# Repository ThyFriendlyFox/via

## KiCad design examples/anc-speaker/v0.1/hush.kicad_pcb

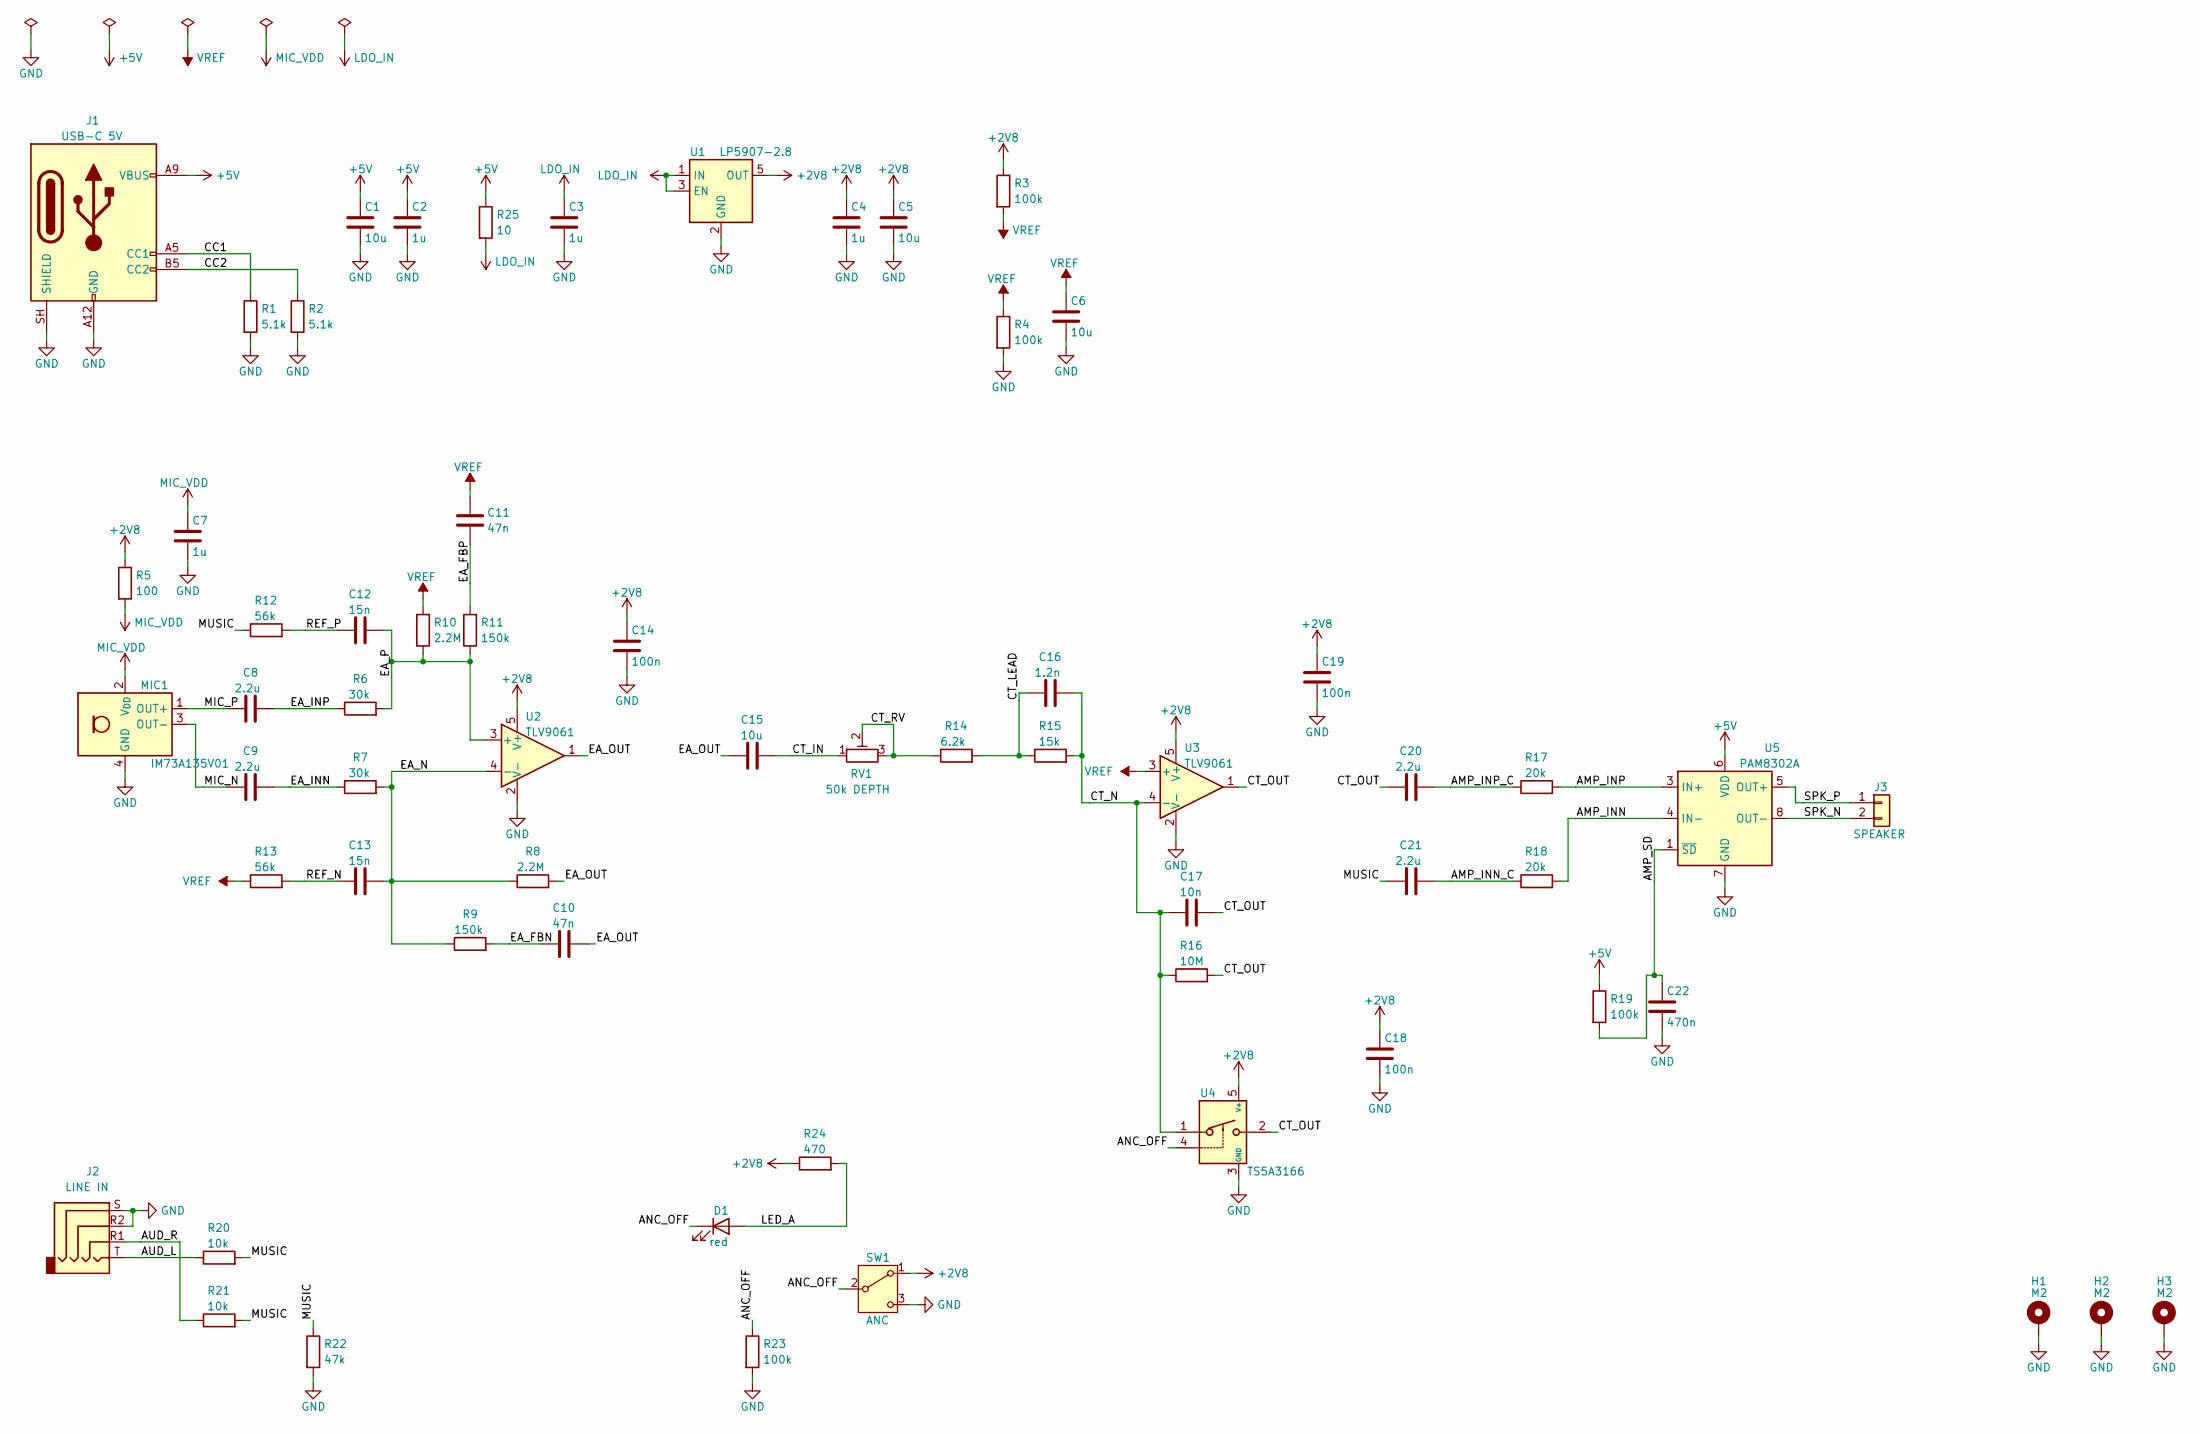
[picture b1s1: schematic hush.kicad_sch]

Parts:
C1: 10u; C_0805_2012Metric
C2, C3, C4, C7: 1u; C_0402_1005Metric
C5, C6, C15: 10u; C_0603_1608Metric
C8, C9, C20, C21: 2.2u; C_0402_1005Metric
C10, C11: 47n; C_0603_1608Metric
C12, C13: 15n; C_0402_1005Metric
C14, C18, C19: 100n; C_0402_1005Metric
C16: 1.2n; C_0402_1005Metric
C17: 10n; C_0402_1005Metric
C22: 470n; C_0402_1005Metric
D1: red; LED_0603_1608Metric
H1, H2, H3: M2; MountingHole_2.2mm_M2_ISO7380_Pad
J1: USB-C 5V; USB_C_Receptacle_GCT_USB4125-xx-x_6P_TopMnt_Horizontal
J2: LINE IN; Jack_3.5mm_PJ320D_Horizontal
J3: SPEAKER; SolderWire-0.25sqmm_1x02_P4.2mm_D0.65mm_OD1.7mm
MIC1: IM73A135V01; Infineon_PG-LLGA-5-2
R1, R2: 5.1k; R_0402_1005Metric
R3, R4, R19, R23: 100k; R_0402_1005Metric
R5: 100; R_0402_1005Metric
R6, R7: 30k; R_0402_1005Metric
R8, R10: 2.2M; R_0402_1005Metric
R9, R11: 150k; R_0402_1005Metric
R12, R13: 56k; R_0402_1005Metric
R14: 6.2k; R_0402_1005Metric
R15: 15k; R_0402_1005Metric
R16: 10M; R_0402_1005Metric
R17, R18: 20k; R_0402_1005Metric
R20, R21: 10k; R_0402_1005Metric
R22: 47k; R_0402_1005Metric
R24: 470; R_0402_1005Metric
R25: 10; R_0402_1005Metric
RV1: 50k DEPTH; Potentiometer_Bourns_TC33X_Vertical
SW1: ANC; SW_SPDT_PCM12
U1: LP5907-2.8; SOT-23-5
U2, U3: TLV9061; SOT-23-5
U4: TS5A3166; SOT-353_SC-70-5
U5: PAM8302A; MSOP-8_3x3mm_P0.65mm

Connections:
+2V8: C4.1, C5.1, C14.1, C18.1, C19.1, R3.1, R5.1, R24.1, SW1.1 (A), U1.5 (OUT), U2.5 (V+), U3.5 (V+), U4.5 (V+)
+5V: C1.1, C2.1, J1.A9 (VBUS), J1.B9 (VBUS), R19.1, R25.1, U5.6 (VDD)
/AMP_INN: R18.2, U5.4 (IN-)
/AMP_INN_C: C21.2, R18.1
/AMP_INP: R17.2, U5.3 (IN+)
/AMP_INP_C: C20.2, R17.1
/AMP_SD: C22.1, R19.2, U5.1 (~SD)
/ANC_OFF: D1.1 (K), R23.1, SW1.2 (B), U4.4
/AUD_L: J2.T, R20.1
/AUD_R: J2.R1, R21.1
/CC1: J1.A5 (CC1), R1.1
/CC2: J1.B5 (CC2), R2.1
/CT_IN: C15.2, RV1.1
/CT_LEAD: C16.1, R14.2, R15.1
/CT_N: C16.2, C17.1, R15.2, R16.1, U3.4 (-), U4.1
/CT_OUT: C17.2, C20.1, R16.2, U3.1, U4.2
/CT_RV: R14.1, RV1.2, RV1.3
/EA_FBN: C10.1, R9.2
/EA_FBP: C11.1, R11.2
/EA_INN: C9.2, R7.1
/EA_INP: C8.2, R6.1
/EA_N: C13.2, R7.2, R8.1, R9.1, U2.4 (-)
/EA_OUT: C10.2, C15.1, R8.2, U2.1
/EA_P: C12.2, R6.2, R10.1, R11.1, U2.3 (+)
/LED_A: D1.2 (A), R24.2
/MIC_N: C9.1, MIC1.3 (OUT-)
/MIC_P: C8.1, MIC1.1 (OUT+)
/MUSIC: C21.1, R12.1, R20.2, R21.2, R22.1
/REF_N: C13.1, R13.2
/REF_P: C12.1, R12.2
/SPK_N: J3.2, U5.8 (OUT-)
/SPK_P: J3.1, U5.5 (OUT+)
GND: C1.2, C2.2, C3.2, C4.2, C5.2, C6.2, C7.2, C14.2, C18.2, C19.2, C22.2, H1.1, H2.1, H3.1, J1.A12 (GND), J1.B12 (GND), J1.SH (SHIELD), J2.R2, J2.S, MIC1.4 (GND), MIC1.5 (GND), R1.2, R2.2, R4.2, R22.2, R23.2, SW1.3 (C), U1.2 (GND), U2.2 (V-), U3.2 (V-), U4.3 (GND), U5.7 (GND)
LDO_IN: C3.1, R25.2, U1.1 (IN), U1.3 (EN)
MIC_VDD: C7.1, MIC1.2 (V_{DD}), R5.2
VREF: C6.1, C11.2, R3.2, R4.1, R10.2, R13.1, U3.3 (+)

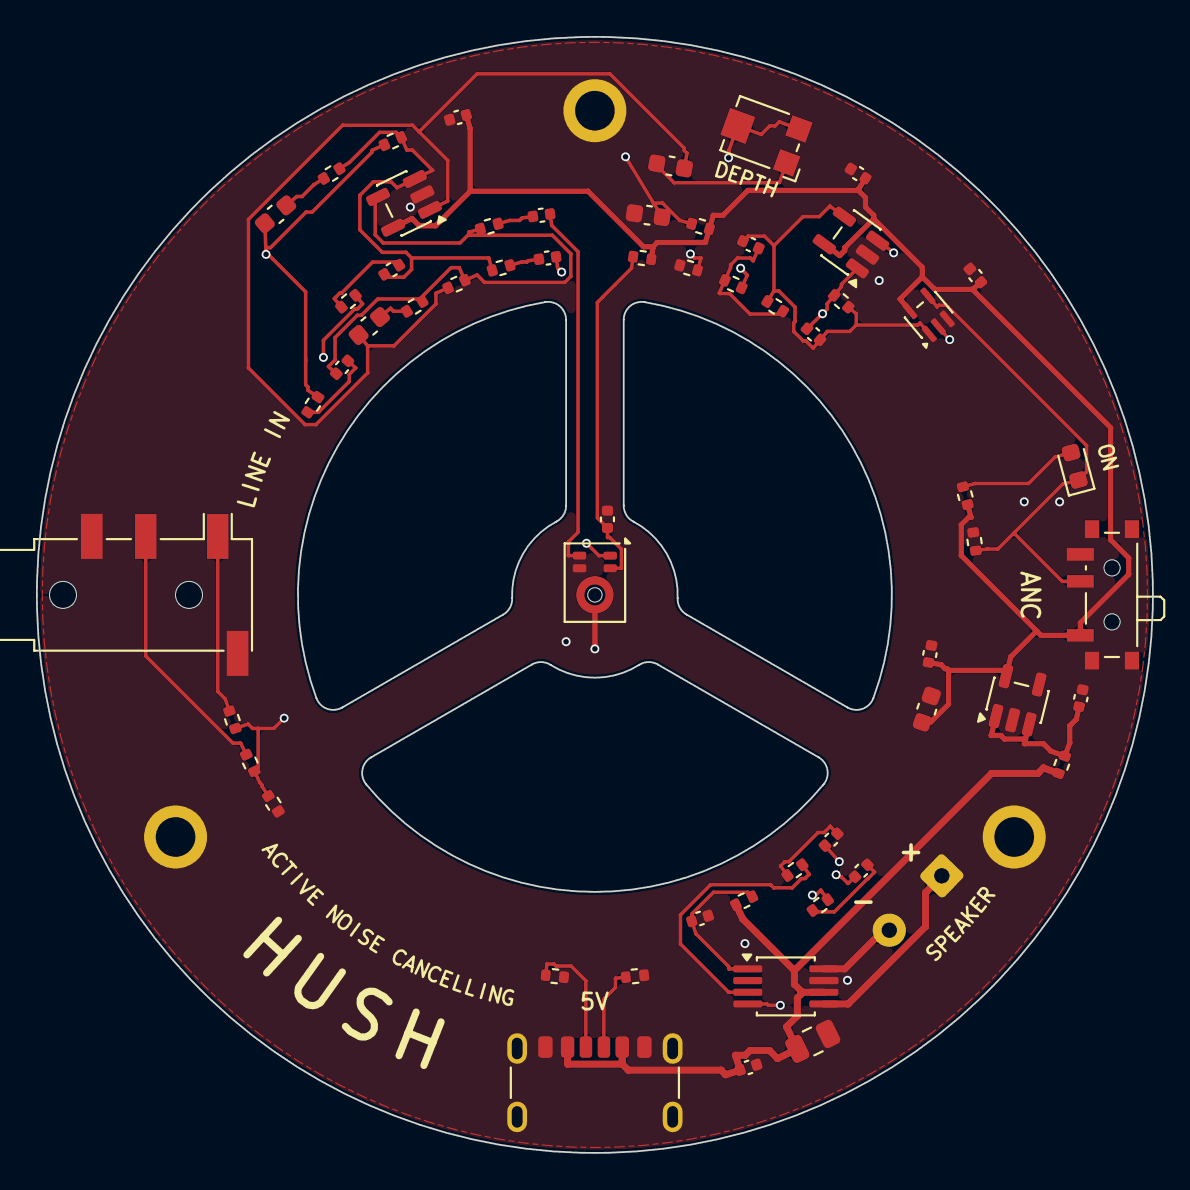
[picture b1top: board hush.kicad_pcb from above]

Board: 4 copper layers, 62.0 x 62.0 mm, 62 parts (0 on the bottom side), 36 nets.

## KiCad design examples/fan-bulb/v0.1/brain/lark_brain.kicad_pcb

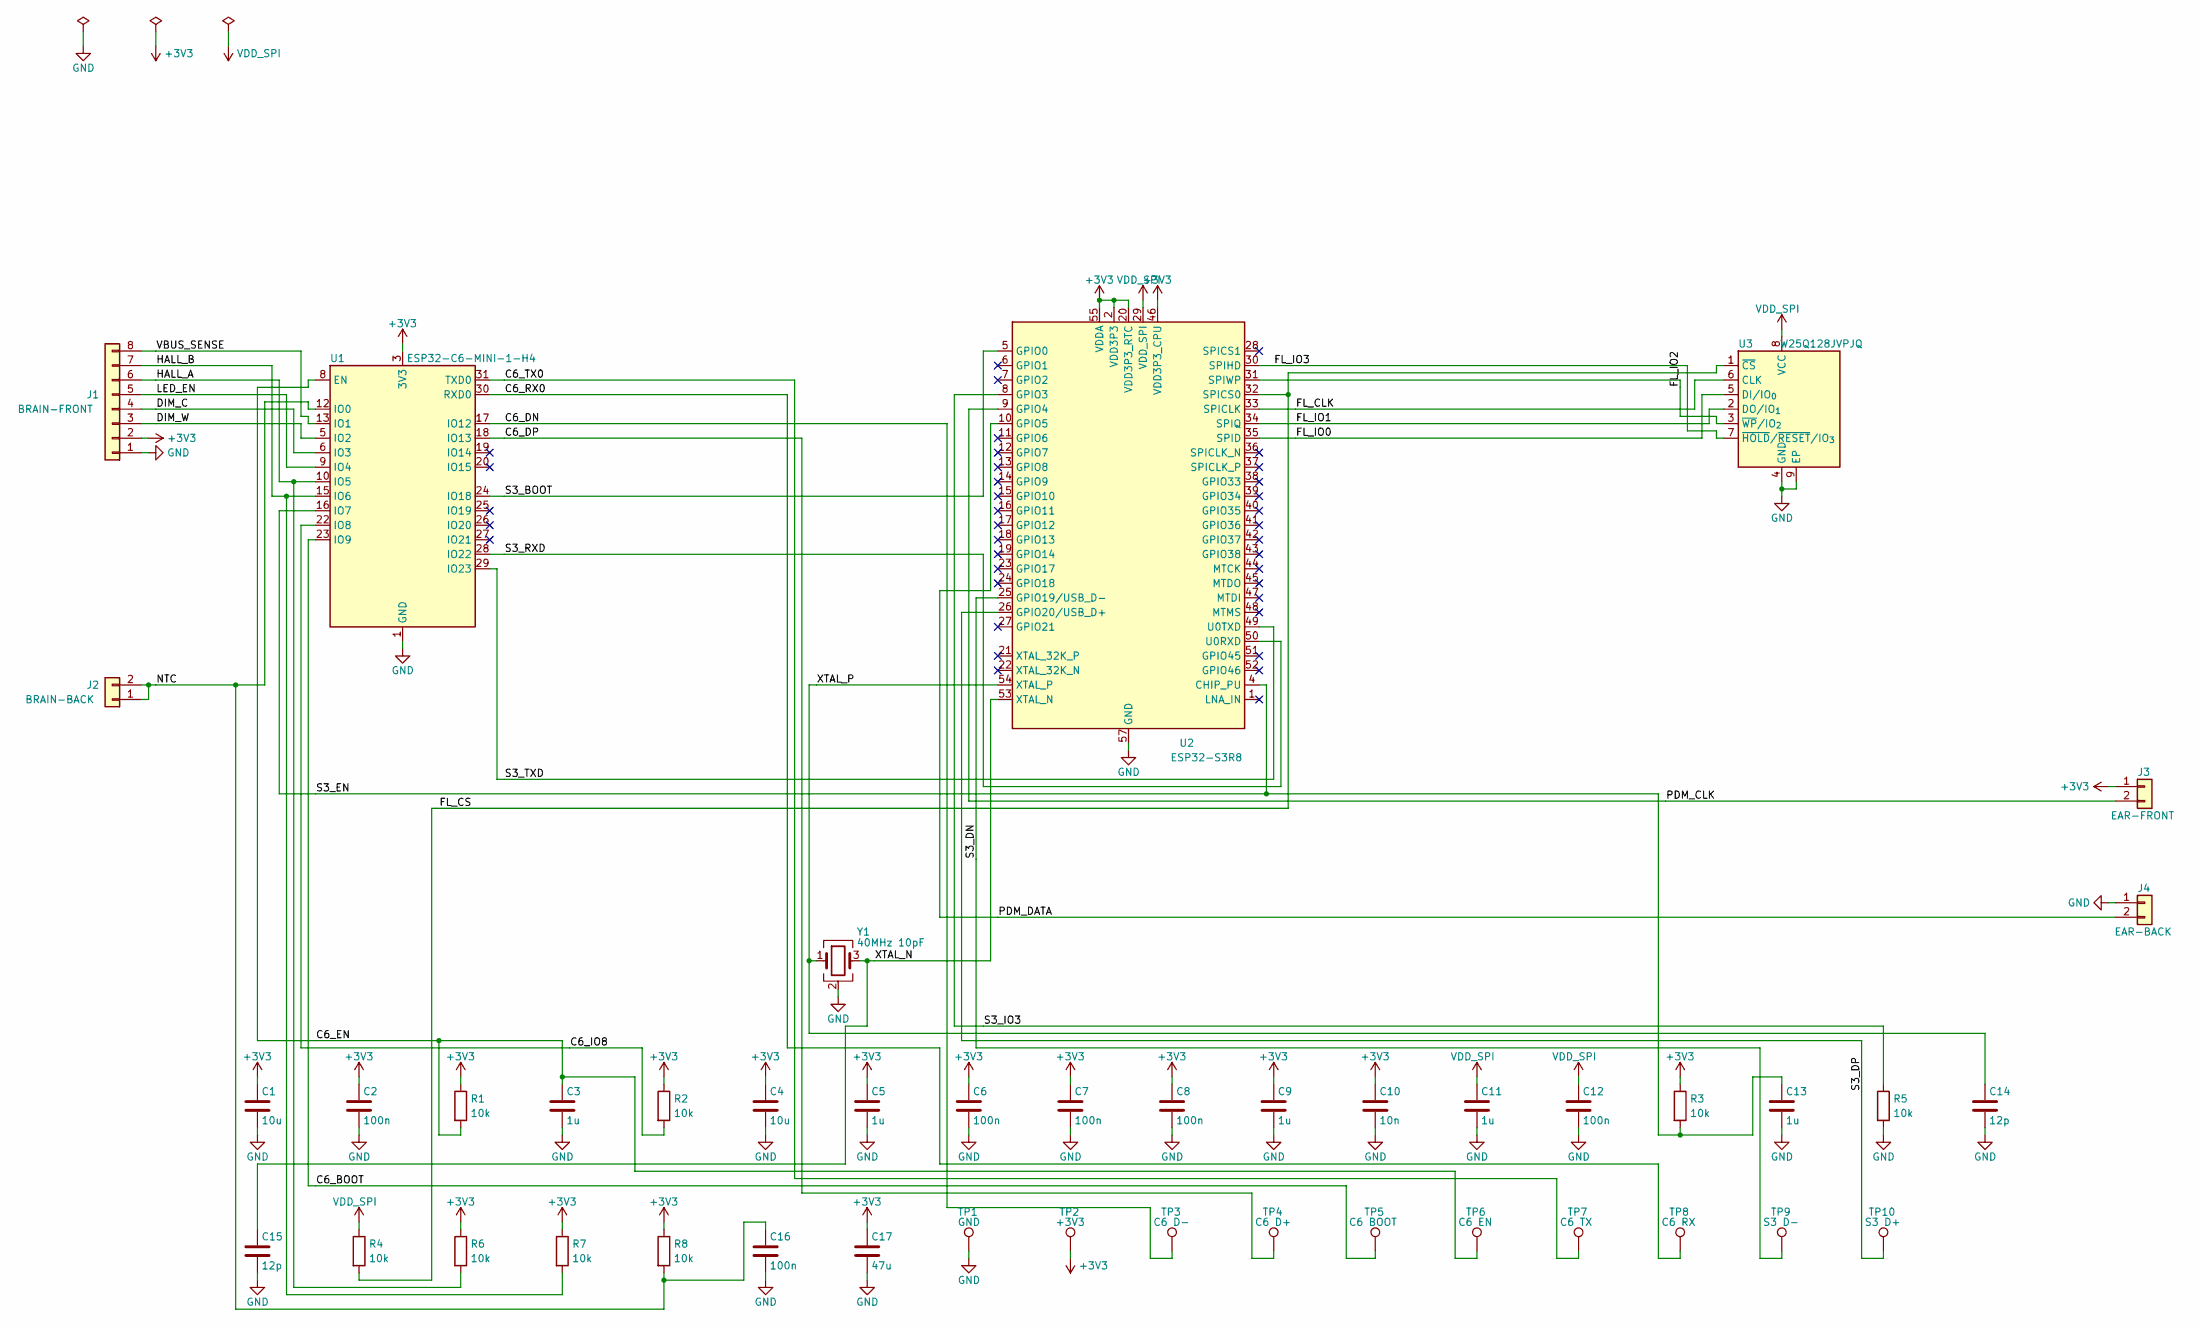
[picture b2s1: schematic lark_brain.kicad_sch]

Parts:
C1, C4: 10u; C_0603_1608Metric
C2, C6, C7, C8, C12, C16: 100n; C_0402_1005Metric
C3, C5, C9, C11, C13: 1u; C_0402_1005Metric
C10: 10n; C_0402_1005Metric
C14, C15: 12p; C_0402_1005Metric
C17: 47u; C_1206_3216Metric
J1: BRAIN-FRONT; Tongue_brain-front
J2: BRAIN-BACK; Tongue_brain-back
J3: EAR-FRONT; Tongue_ear-front
J4: EAR-BACK; Tongue_ear-back
R1, R2, R3, R4, R5, R6, R7, R8: 10k; R_0402_1005Metric
TP1: GND; TestPoint_Pad_D1.0mm
TP2: +3V3; TestPoint_Pad_D1.0mm
TP3: C6 D-; TestPoint_Pad_D1.0mm
TP4: C6 D+; TestPoint_Pad_D1.0mm
TP5: C6 BOOT; TestPoint_Pad_D1.0mm
TP6: C6 EN; TestPoint_Pad_D1.0mm
TP7: C6 TX; TestPoint_Pad_D1.0mm
TP8: C6 RX; TestPoint_Pad_D1.0mm
TP9: S3 D-; TestPoint_Pad_D1.0mm
TP10: S3 D+; TestPoint_Pad_D1.0mm
U1: ESP32-C6-MINI-1-H4; ESP32-C6-MINI-1
U2: ESP32-S3R8; QFN-56-1EP_7x7mm_P0.4mm_EP4x4mm
U3: W25Q128JVPJQ; WSON-8-1EP_6x5mm_P1.27mm_EP3.4x4.3mm
Y1: 40MHz 10pF; Crystal_SMD_2016-4Pin_2.0x1.6mm

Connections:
+3V3: C1.1, C2.1, C4.1, C5.1, C6.1, C7.1, C8.1, C9.1, C10.1, C17.1, J1.2, J3.1, R1.1, R2.1, R3.1, R6.1, R7.1, R8.1, TP2.1, U1.3 (3V3), U2.2 (VDD3P3), U2.3 (VDD3P3), U2.20 (VDD3P3_RTC), U2.46 (VDD3P3_CPU), U2.55 (VDDA), U2.56 (VDDA)
/C6_BOOT: TP5.1, U1.23 (IO9)
/C6_DN: TP3.1, U1.17 (IO12)
/C6_DP: TP4.1, U1.18 (IO13)
/C6_EN: C3.1, R1.2, TP6.1, U1.8 (EN)
/C6_IO8: R2.2, U1.22 (IO8)
/C6_RX0: TP8.1, U1.30 (RXD0)
/C6_TX0: TP7.1, U1.31 (TXD0)
/DIM_C: J1.4, U1.6 (IO3)
/DIM_W: J1.3, U1.5 (IO2)
/FL_CLK: U2.33 (SPICLK), U3.6 (CLK)
/FL_CS: R4.2, U2.32 (SPICS0), U3.1 (~CS)
/FL_IO0: U2.35 (SPID), U3.5 (DI/IO_{0})
/FL_IO1: U2.34 (SPIQ), U3.2 (DO/IO_{1})
/FL_IO2: U2.31 (SPIWP), U3.3 (~WP/IO_{2})
/FL_IO3: U2.30 (SPIHD), U3.7 (~HOLD/~RESET/IO_{3})
/HALL_A: J1.6, R6.2, U1.10 (IO5)
/HALL_B: J1.7, R7.2, U1.15 (IO6)
/LED_EN: J1.5, U1.9 (IO4)
/NTC: C16.1, J2.1, J2.2, R8.2, U1.12 (IO0)
/PDM_CLK: J3.2, U2.9 (GPIO4)
/PDM_DATA: J4.2, U2.10 (GPIO5)
/S3_BOOT: U1.24 (IO18), U2.5 (GPIO0)
/S3_DN: TP9.1, U2.25 (GPIO19/USB_D-)
/S3_DP: TP10.1, U2.26 (GPIO20/USB_D+)
/S3_EN: C13.1, R3.2, U1.16 (IO7), U2.4 (CHIP_PU)
/S3_IO3: R5.1, U2.8 (GPIO3)
/S3_RXD: U1.28 (IO22), U2.50 (U0RXD)
/S3_TXD: U1.29 (IO23), U2.49 (U0TXD)
/VBUS_SENSE: J1.8, U1.13 (IO1)
/XTAL_N: C15.1, U2.53 (XTAL_N), Y1.3
/XTAL_P: C14.1, U2.54 (XTAL_P), Y1.1
GND: C1.2, C2.2, C3.2, C4.2, C5.2, C6.2, C7.2, C8.2, C9.2, C10.2, C11.2, C12.2, C13.2, C14.2, C15.2, C16.2, C17.2, J1.1, J4.1, R5.2, TP1.1, U1.1 (GND), U1.2 (GND), U1.11 (GND), U1.14 (GND), U1.36 (GND), U1.37 (GND), U1.38 (GND), U1.39 (GND), U1.40 (GND), U1.41 (GND), U1.42 (GND), U1.43 (GND), U1.44 (GND), U1.45 (GND), U1.46 (GND), U1.47 (GND), U1.48 (GND), U1.49 (GND), U1.50 (GND), U1.51 (GND), U1.52 (GND), U1.53 (GND), U2.57 (GND), U3.4 (GND), U3.9 (EP), Y1.2 (G), Y1.4 (G)
VDD_SPI: C11.1, C12.1, R4.1, U2.29 (VDD_SPI), U3.8 (VCC)

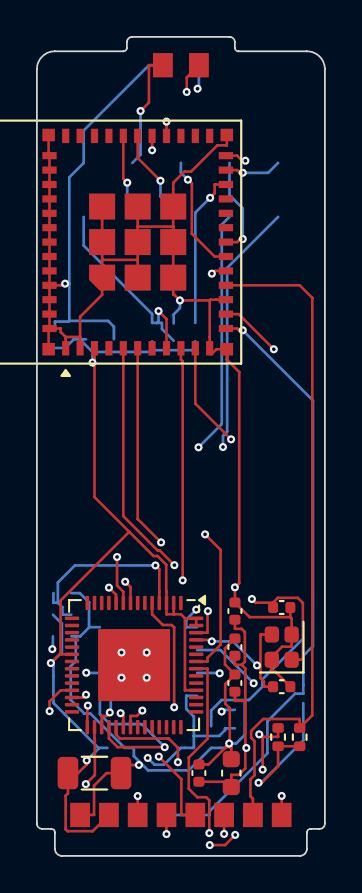
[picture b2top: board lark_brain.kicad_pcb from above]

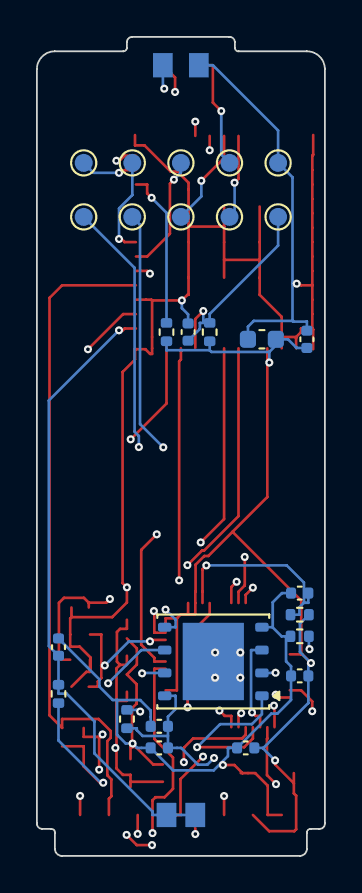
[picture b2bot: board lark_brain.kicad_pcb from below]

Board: 4 copper layers, 16.0 x 45.5 mm, 43 parts (28 on the bottom side), 34 nets.

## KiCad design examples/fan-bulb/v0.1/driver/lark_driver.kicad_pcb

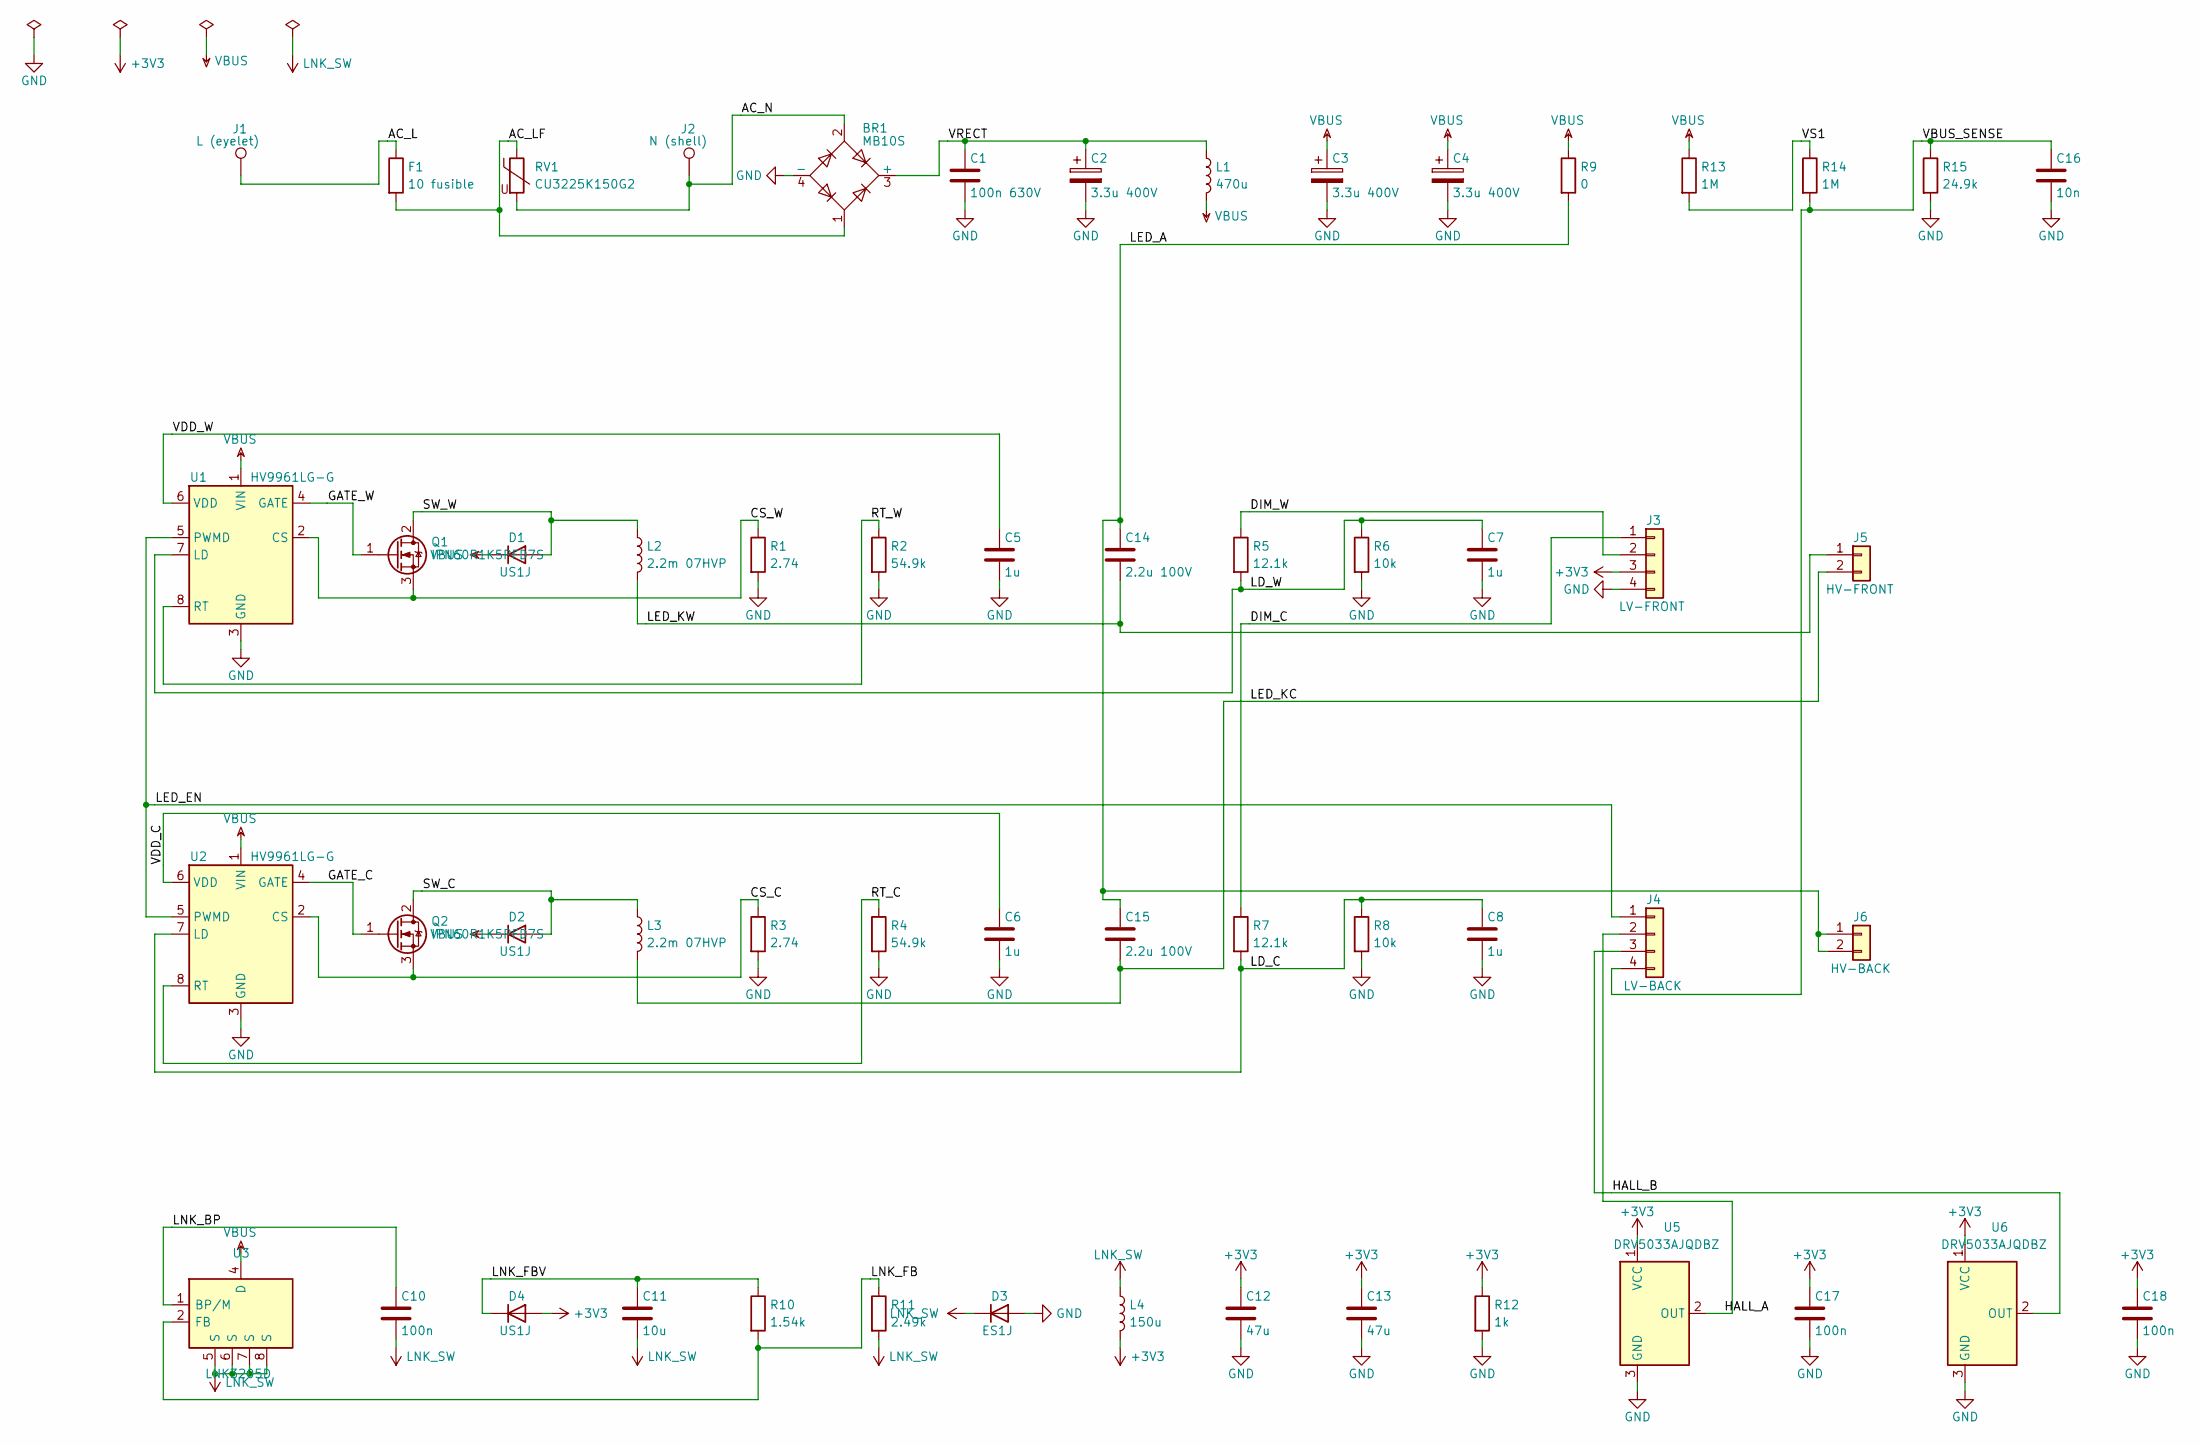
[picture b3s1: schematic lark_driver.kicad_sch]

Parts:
BR1: MB10S; TO-269AA
C1: 100n 630V; C_1812_4532Metric
C2, C3, C4: 3.3u 400V; CP_Radial_D8.0mm_L11.5mm_P3.50mm_Lying
C5, C6, C7, C8: 1u; C_0402_1005Metric
C10: 100n; C_0603_1608Metric
C11: 10u; C_0805_2012Metric
C12, C13: 47u; C_1206_3216Metric
C14, C15: 2.2u 100V; C_1206_3216Metric
C16: 10n; C_0402_1005Metric
C17, C18: 100n; C_0402_1005Metric
D1, D2, D4: US1J; D_SMA
D3: ES1J; D_SMA
F1: 10 fusible; R_MELF_MMB-0207
J1: L (eyelet); TestPoint_THTPad_D2.0mm_Drill1.0mm
J2: N (shell); TestPoint_THTPad_D2.0mm_Drill1.0mm
J3: LV-FRONT; Tongue_lv-front
J4: LV-BACK; Tongue_lv-back
J5: HV-FRONT; Tongue_hv-front
J6: HV-BACK; Tongue_hv-back
L1: 470u; L_Bourns_SDR0604
L2, L3: 2.2m 07HVP; L_Radial_D9.5mm_P5.00mm_Fastron_07HVP
L4: 150u; L_Bourns_SDR0604
Q1, Q2: IPN60R1K5PFD7S; SOT-223-3_TabPin2
R1, R3: 2.74; R_1206_3216Metric
R2, R4: 54.9k; R_0402_1005Metric
R5, R7: 12.1k; R_0402_1005Metric
R6, R8: 10k; R_0402_1005Metric
R9: 0; R_1206_3216Metric
R10: 1.54k; R_0402_1005Metric
R11: 2.49k; R_0402_1005Metric
R12: 1k; R_0603_1608Metric
R13, R14: 1M; R_1206_3216Metric
R15: 24.9k; R_0402_1005Metric
RV1: CU3225K150G2; RV_SMD_TDK_CU3225
U1, U2: HV9961LG-G; SOIC-8_3.9x4.9mm_P1.27mm
U3: LNK3205D; PowerIntegrations_SO-8C
U5, U6: DRV5033AJQDBZ; SOT-23

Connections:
+3V3: C12.1, C13.1, C17.1, C18.1, D4.2 (A), J3.3, L4.2, R12.1, U5.1 (VCC), U6.1 (VCC)
/AC_L: F1.1, J1.1
/AC_LF: BR1.1, F1.2, RV1.1
/AC_N: BR1.2, J2.1, RV1.2
/CS_C: Q2.3 (S), R3.1, U2.2 (CS)
/CS_W: Q1.3 (S), R1.1, U1.2 (CS)
/DIM_C: J3.1, R7.1
/DIM_W: J3.2, R5.1
/GATE_C: Q2.1 (G), U2.4 (GATE)
/GATE_W: Q1.1 (G), U1.4 (GATE)
/HALL_A: J4.2, U5.2 (OUT)
/HALL_B: J4.3, U6.2 (OUT)
/LD_C: C8.1, R7.2, R8.1, U2.7 (LD)
/LD_W: C7.1, R5.2, R6.1, U1.7 (LD)
/LED_A: C14.1, C15.1, J6.1, J6.2, R9.2
/LED_EN: J4.1, U1.5 (PWMD), U2.5 (PWMD)
/LED_KC: C15.2, J5.2, L3.2
/LED_KW: C14.2, J5.1, L2.2
/LNK_BP: C10.1, U3.1 (BP/M)
/LNK_FB: R10.2, R11.1, U3.2 (FB)
/LNK_FBV: C11.1, D4.1 (K), R10.1
/RT_C: R4.1, U2.8 (RT)
/RT_W: R2.1, U1.8 (RT)
/SW_C: D2.2 (A), L3.1, Q2.2 (D)
/SW_W: D1.2 (A), L2.1, Q1.2 (D)
/VBUS_SENSE: C16.1, J4.4, R14.2, R15.1
/VDD_C: C6.1, U2.6 (VDD)
/VDD_W: C5.1, U1.6 (VDD)
/VRECT: BR1.3 (+), C1.1, C2.1, L1.1
/VS1: R13.2, R14.1
GND: BR1.4 (-), C1.2, C2.2, C3.2, C4.2, C5.2, C6.2, C7.2, C8.2, C12.2, C13.2, C16.2, C17.2, C18.2, D3.2 (A), J3.4, R1.2, R2.2, R3.2, R4.2, R6.2, R8.2, R12.2, R15.2, U1.3 (GND), U2.3 (GND), U5.3 (GND), U6.3 (GND)
LNK_SW: C10.2, C11.2, D3.1 (K), L4.1, R11.2, U3.5 (S), U3.6 (S), U3.7 (S), U3.8 (S)
VBUS: C3.1, C4.1, D1.1 (K), D2.1 (K), L1.2, R9.1, R13.1, U1.1 (VIN), U2.1 (VIN), U3.4 (D)

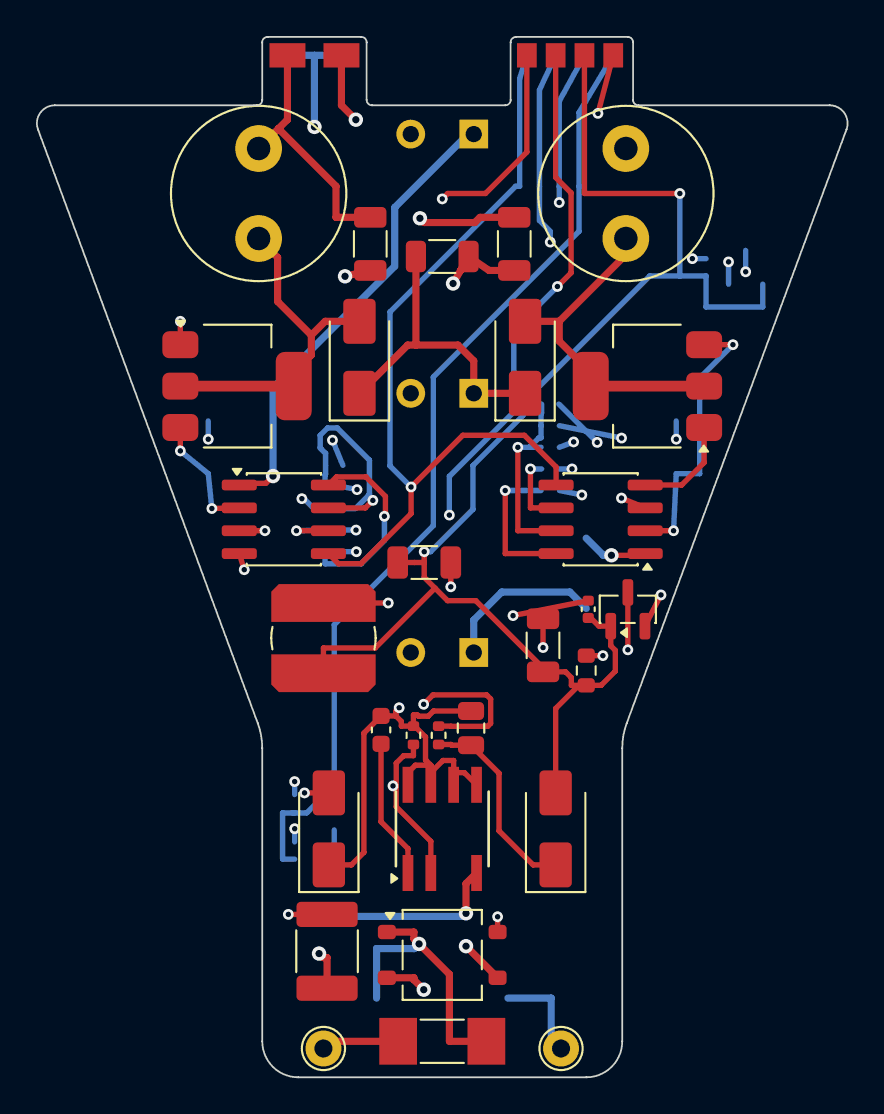
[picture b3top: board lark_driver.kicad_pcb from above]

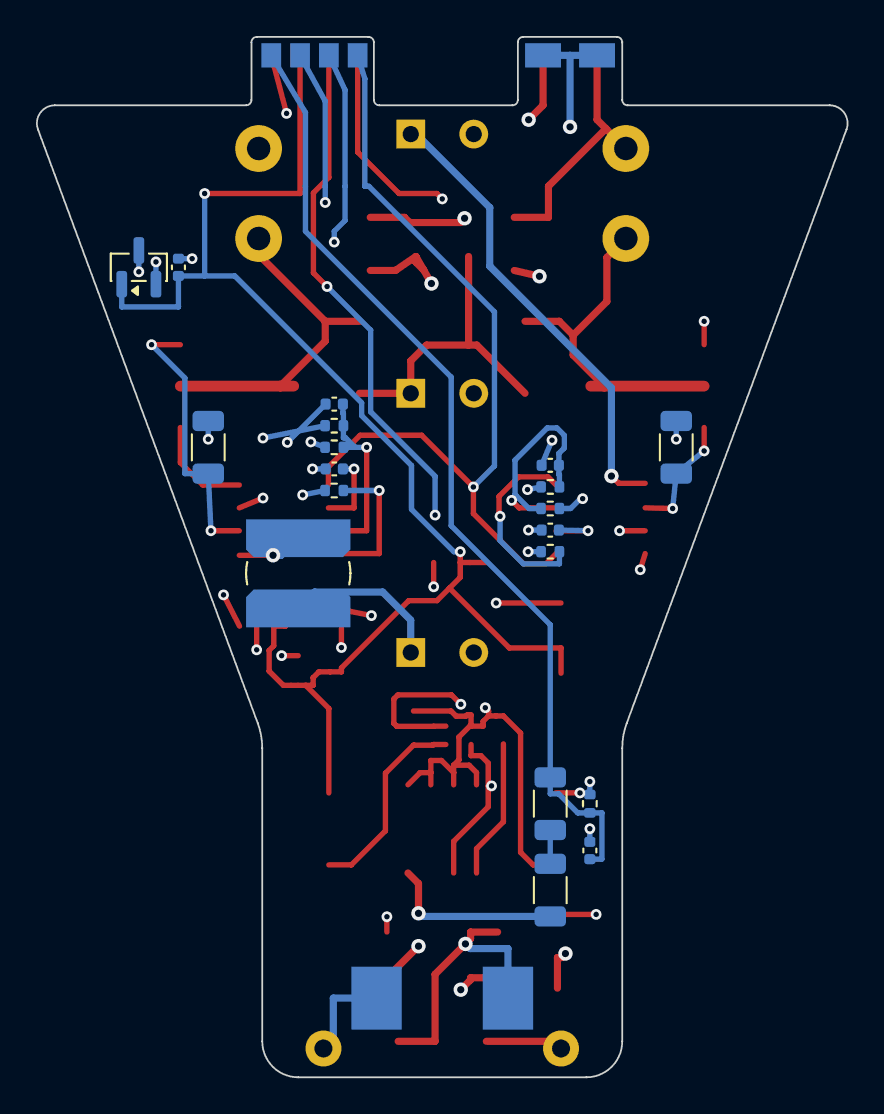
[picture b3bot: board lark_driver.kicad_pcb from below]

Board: 4 copper layers, 45.0 x 57.8 mm, 56 parts (25 on the bottom side), 33 nets.

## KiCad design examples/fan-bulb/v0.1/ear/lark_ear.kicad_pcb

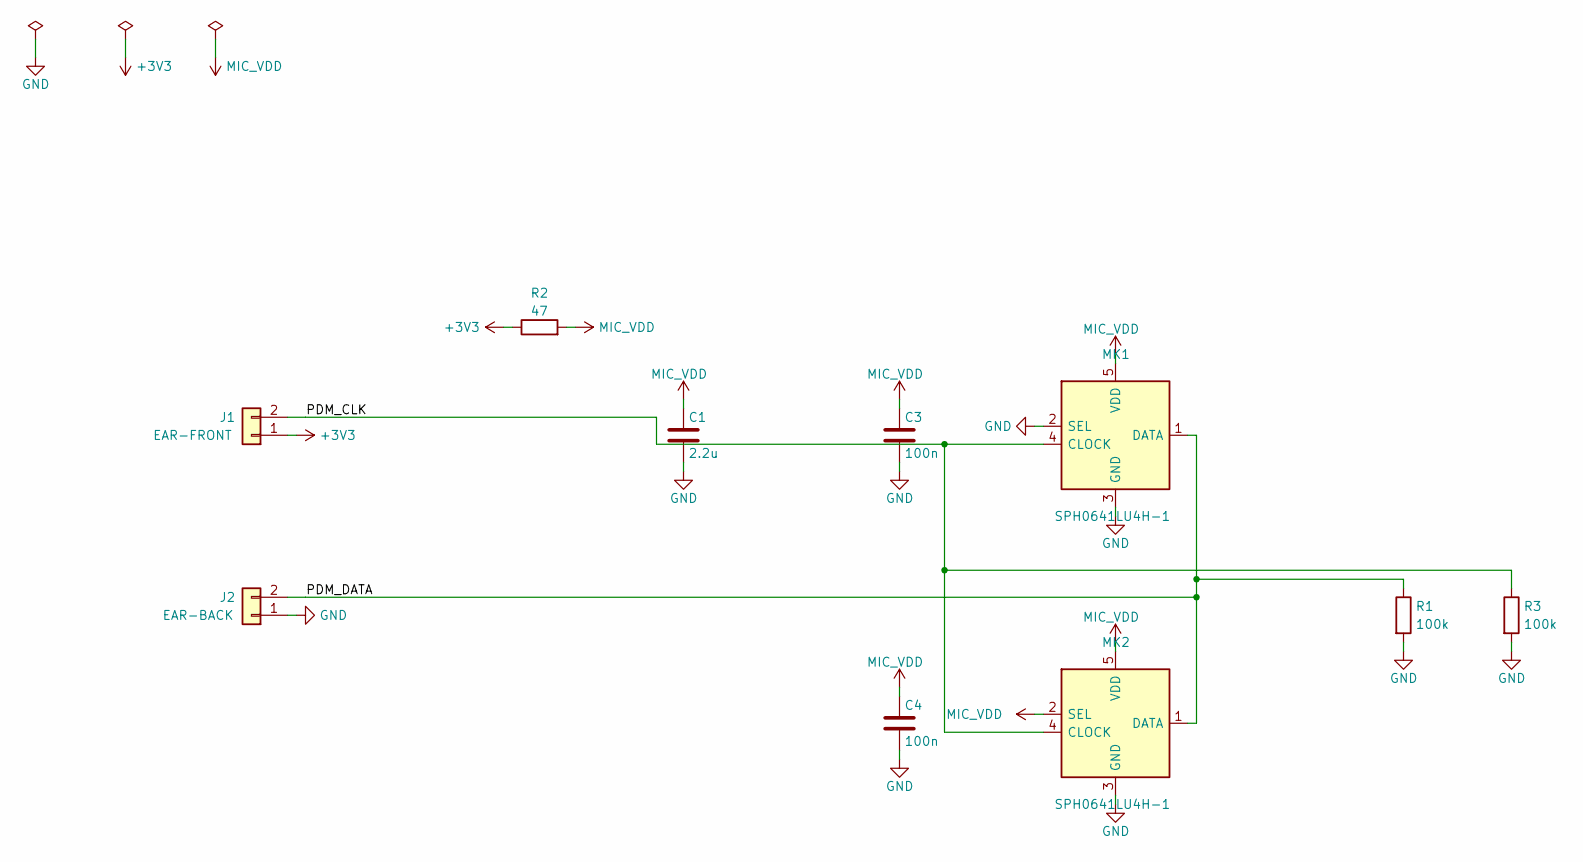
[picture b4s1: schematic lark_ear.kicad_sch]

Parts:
C1: 2.2u; C_0402_1005Metric
C3, C4: 100n; C_0402_1005Metric
J1: EAR-FRONT; SlotPads_ear-front
J2: EAR-BACK; SlotPads_ear-back
MK1, MK2: SPH0641LU4H-1; Knowles_LGA-5_3.5x2.65mm
R1, R3: 100k; R_0402_1005Metric
R2: 47; R_0402_1005Metric

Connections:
+3V3: J1.1, R2.1
/PDM_CLK: J1.2, MK1.4 (CLOCK), MK2.4 (CLOCK), R3.1
/PDM_DATA: J2.2, MK1.1 (DATA), MK2.1 (DATA), R1.1
GND: C1.2, C3.2, C4.2, J2.1, MK1.2 (SEL), MK1.3 (GND), MK2.3 (GND), R1.2, R3.2
MIC_VDD: C1.1, C3.1, C4.1, MK1.5 (VDD), MK2.2 (SEL), MK2.5 (VDD), R2.2

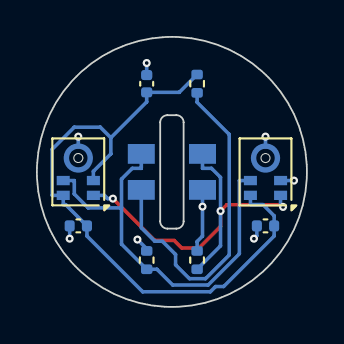
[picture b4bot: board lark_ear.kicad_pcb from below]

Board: 2 copper layers, 15.0 x 15.0 mm, 10 parts (10 on the bottom side), 5 nets.

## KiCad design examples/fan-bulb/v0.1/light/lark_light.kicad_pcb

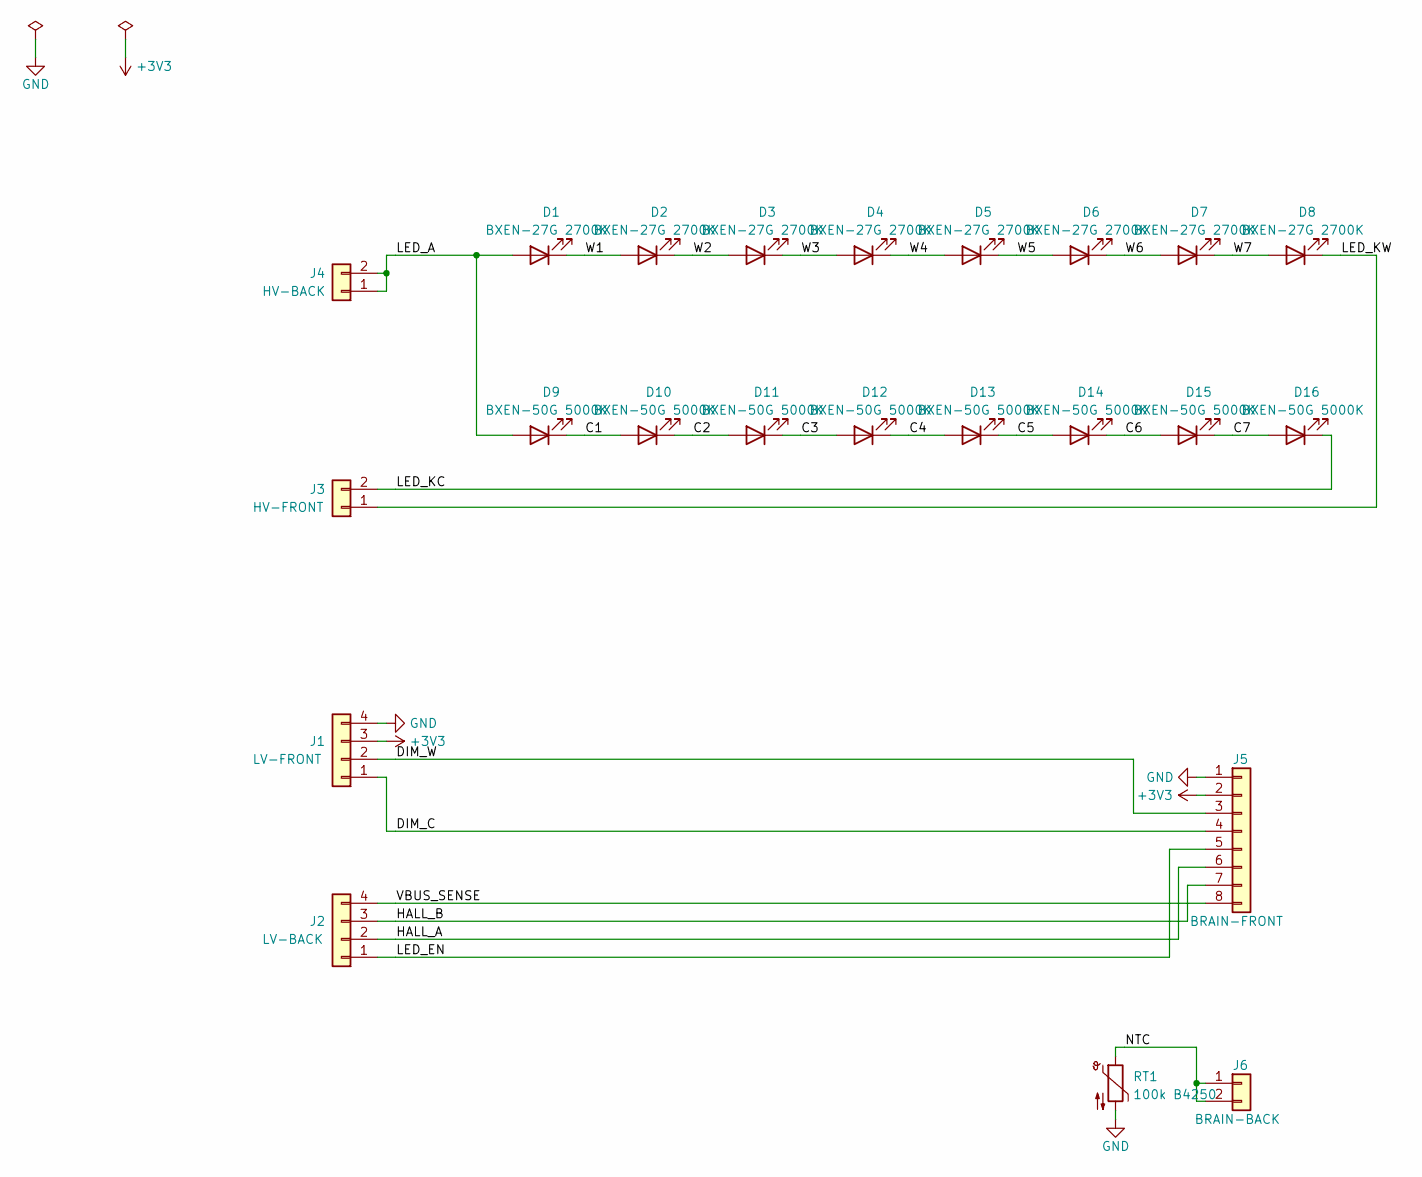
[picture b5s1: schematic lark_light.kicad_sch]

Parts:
D1, D2, D3, D4, D5, D6, D7, D8: BXEN-27G 2700K; LED_PLCC_2835
D9, D10, D11, D12, D13, D14, D15, D16: BXEN-50G 5000K; LED_PLCC_2835
J1: LV-FRONT; SlotPads_lv-front
J2: LV-BACK; SlotPads_lv-back
J3: HV-FRONT; SlotPads_hv-front
J4: HV-BACK; SlotPads_hv-back
J5: BRAIN-FRONT; SlotPads_brain-front
J6: BRAIN-BACK; SlotPads_brain-back
RT1: 100k B4250; R_0402_1005Metric

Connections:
+3V3: J1.3, J5.2
/C1: D9.1 (K), D10.2 (A)
/C2: D10.1 (K), D11.2 (A)
/C3: D11.1 (K), D12.2 (A)
/C4: D12.1 (K), D13.2 (A)
/C5: D13.1 (K), D14.2 (A)
/C6: D14.1 (K), D15.2 (A)
/C7: D15.1 (K), D16.2 (A)
/DIM_C: J1.1, J5.4
/DIM_W: J1.2, J5.3
/HALL_A: J2.2, J5.6
/HALL_B: J2.3, J5.7
/LED_A: D1.2 (A), D9.2 (A), J4.1, J4.2
/LED_EN: J2.1, J5.5
/LED_KC: D16.1 (K), J3.2
/LED_KW: D8.1 (K), J3.1
/NTC: J6.1, J6.2, RT1.1
/VBUS_SENSE: J2.4, J5.8
/W1: D1.1 (K), D2.2 (A)
/W2: D2.1 (K), D3.2 (A)
/W3: D3.1 (K), D4.2 (A)
/W4: D4.1 (K), D5.2 (A)
/W5: D5.1 (K), D6.2 (A)
/W6: D6.1 (K), D7.2 (A)
/W7: D7.1 (K), D8.2 (A)
GND: J1.4, J5.1, RT1.2
